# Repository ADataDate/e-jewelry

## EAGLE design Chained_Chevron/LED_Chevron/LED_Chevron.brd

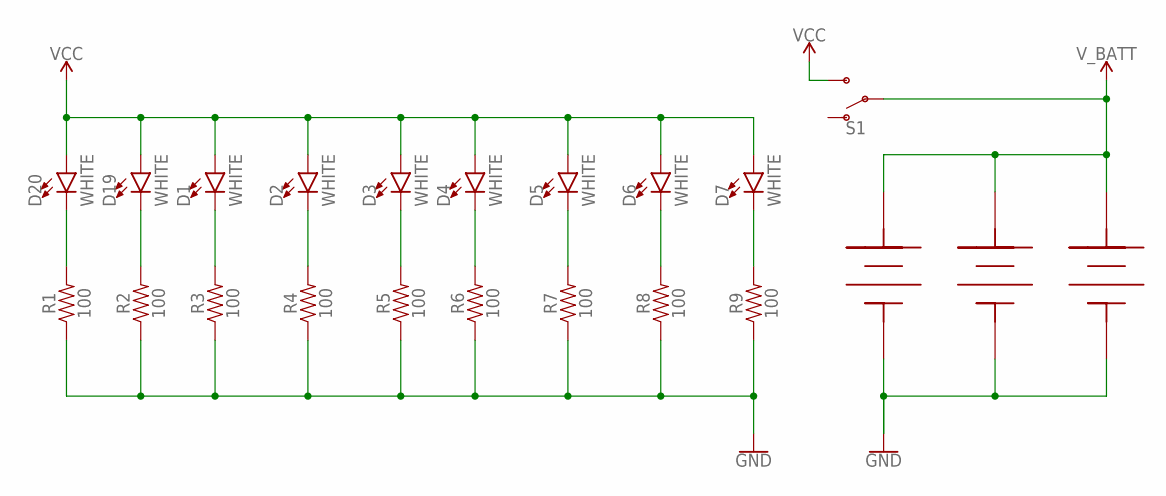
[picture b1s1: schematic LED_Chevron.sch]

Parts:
D1, D2, D3, D4, D5, D6, D7, D19, D20: WHITE; LED-1206
R1, R2, R3, R4, R5, R6, R7, R8, R9: 100; 0603
S1: SWITCH-SPDT-SMD-RIGHT-ANGLE; SWITCH_SPST_SMD_A
U$1, U$2, U$3: 7.8MM_COIN_CELL_BATTERY; 7.8MM_COIN_CELL_BATT

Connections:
GND: R1.1, R2.1, R3.1, R4.1, R5.1, R6.1, R7.1, R8.1, R9.1, U$1.GND (BATT-), U$2.GND (BATT-), U$3.GND (BATT-)
unnamed: D20.C, R1.2
unnamed: D19.C, R2.2
unnamed: D1.C, R3.2
unnamed: D2.C, R4.2
unnamed: D3.C, R5.2
unnamed: D4.C, R6.2
unnamed: D5.C, R7.2
unnamed: D6.C, R8.2
unnamed: D7.C, R9.2
VCC: D1.A, D2.A, D3.A, D4.A, D5.A, D6.A, D7.A, D19.A, D20.A, S1.3 (S)
V_BATT: S1.2, U$1.P$3 (BATT+), U$1.VBATT+ (BATT+), U$2.P$3 (BATT+), U$2.VBATT+ (BATT+), U$3.P$3 (BATT+), U$3.VBATT+ (BATT+)

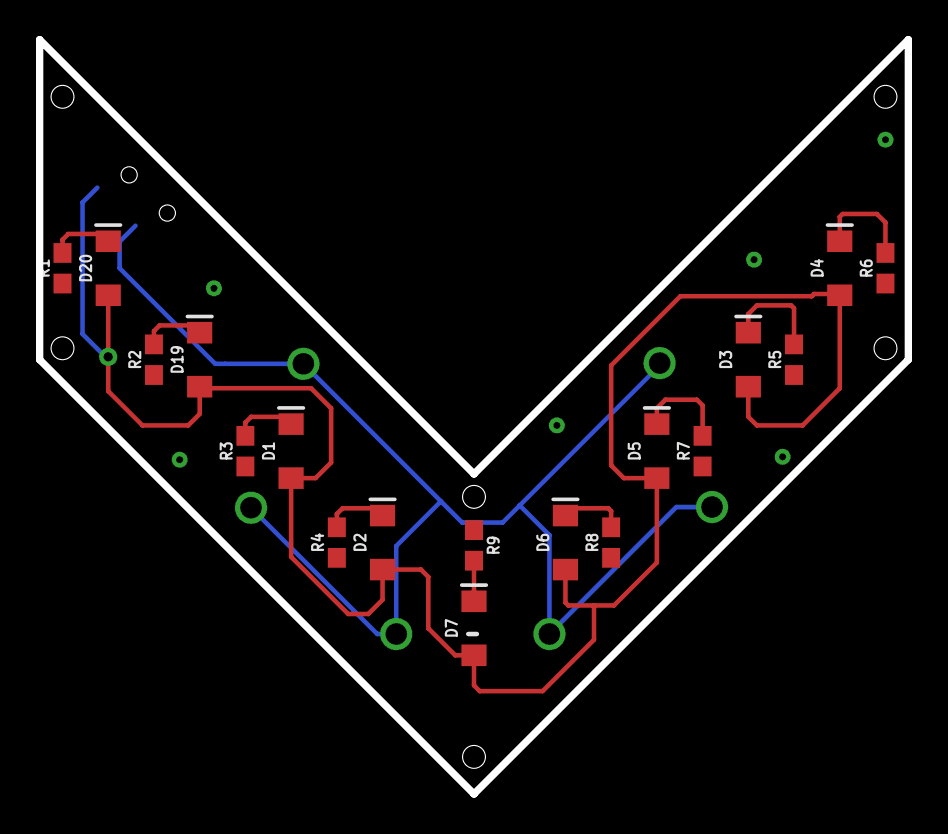
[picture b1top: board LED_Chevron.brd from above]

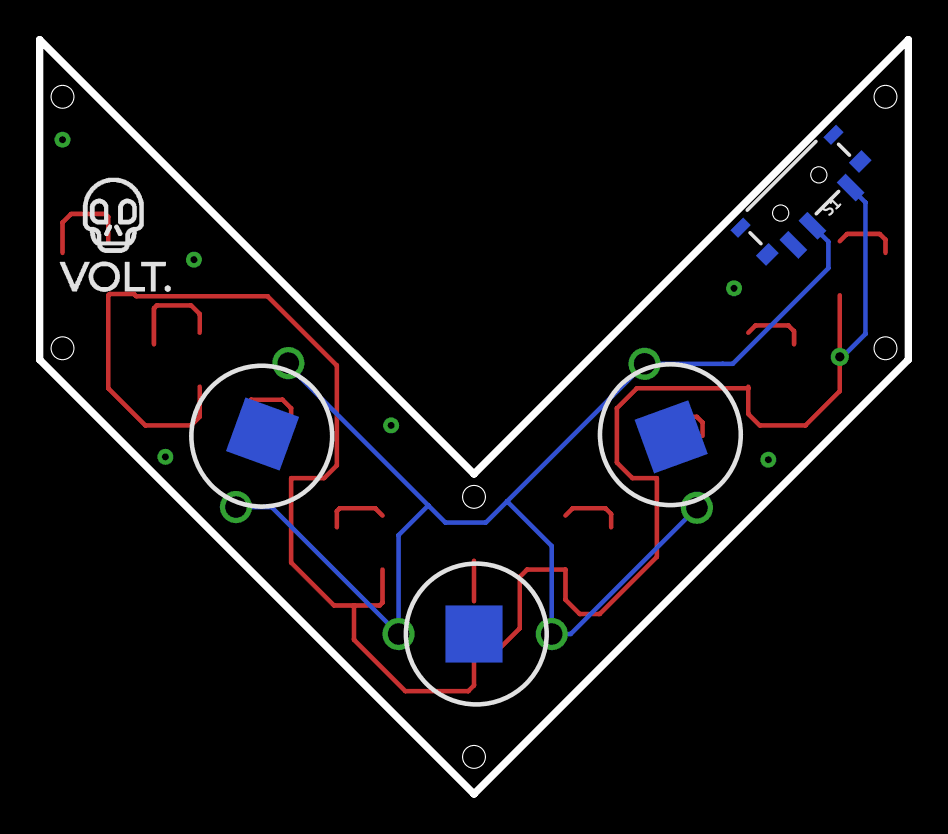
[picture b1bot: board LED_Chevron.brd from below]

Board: 2 copper layers, 48.3 x 41.9 mm, 23 parts (5 on the bottom side), 12 nets.

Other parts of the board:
U$5: VOLT##LOGO#WHITE_#1##PNG

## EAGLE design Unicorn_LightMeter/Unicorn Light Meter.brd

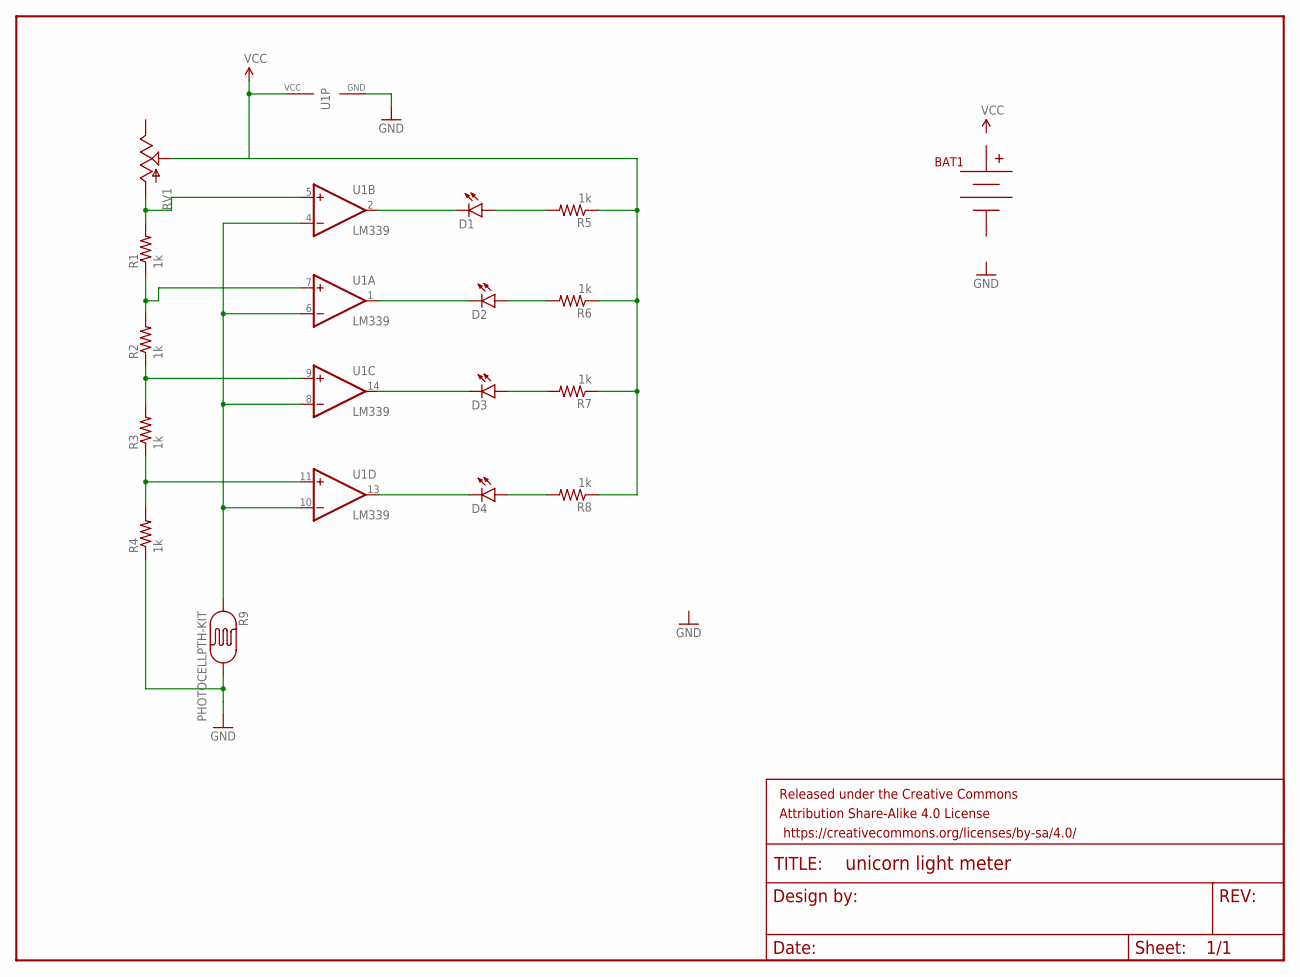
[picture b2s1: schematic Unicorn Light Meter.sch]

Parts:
BAT1: BC9VPCKIT_SOLDERMASK; BC9VPC_KIT
D1, D2, D3, D4: LED5MM
FRAME1: FRAME-LETTER; CREATIVE_COMMONS
R1, R2, R3, R4, R5, R6, R7, R8: 1k; AXIAL-0.3EZ
R9: PHOTOCELLPTH-KIT; PHOTOCELL-KIT
RV1: POT100K_3362U; 3362U
U1: LM339; TSSOP-14

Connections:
GND: R4.P$1 (1), R9.2, U1.12 (GND)
unnamed: D2.A, R6.P$2 (2)
unnamed: D3.A, R7.P$2 (2)
unnamed: D4.K (C), U1.13 (OUT)
unnamed: D3.K (C), U1.14 (OUT)
unnamed: D1.K (C), U1.2 (OUT)
unnamed: D2.K (C), U1.1 (OUT)
unnamed: D1.A, R5.P$2 (2)
unnamed: D4.A, R8.P$2 (2)
unnamed: R1.P$2 (2), RV1.P$3 (A), U1.5 (+IN)
unnamed: R1.P$1 (1), R2.P$2 (2), U1.7 (+IN)
unnamed: R2.P$1 (1), R3.P$2 (2), U1.9 (+IN)
unnamed: R3.P$1 (1), R4.P$2 (2), U1.11 (+IN)
unnamed: R9.1, U1.4 (-IN), U1.6 (-IN), U1.8 (-IN), U1.10 (-IN)
VCC: R5.P$1 (1), R6.P$1 (1), R7.P$1 (1), R8.P$1 (1), RV1.P$2 (S), U1.3 (VCC)

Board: 2 copper layers, 17 parts (1 on the bottom side), 15 nets, no tracks yet.

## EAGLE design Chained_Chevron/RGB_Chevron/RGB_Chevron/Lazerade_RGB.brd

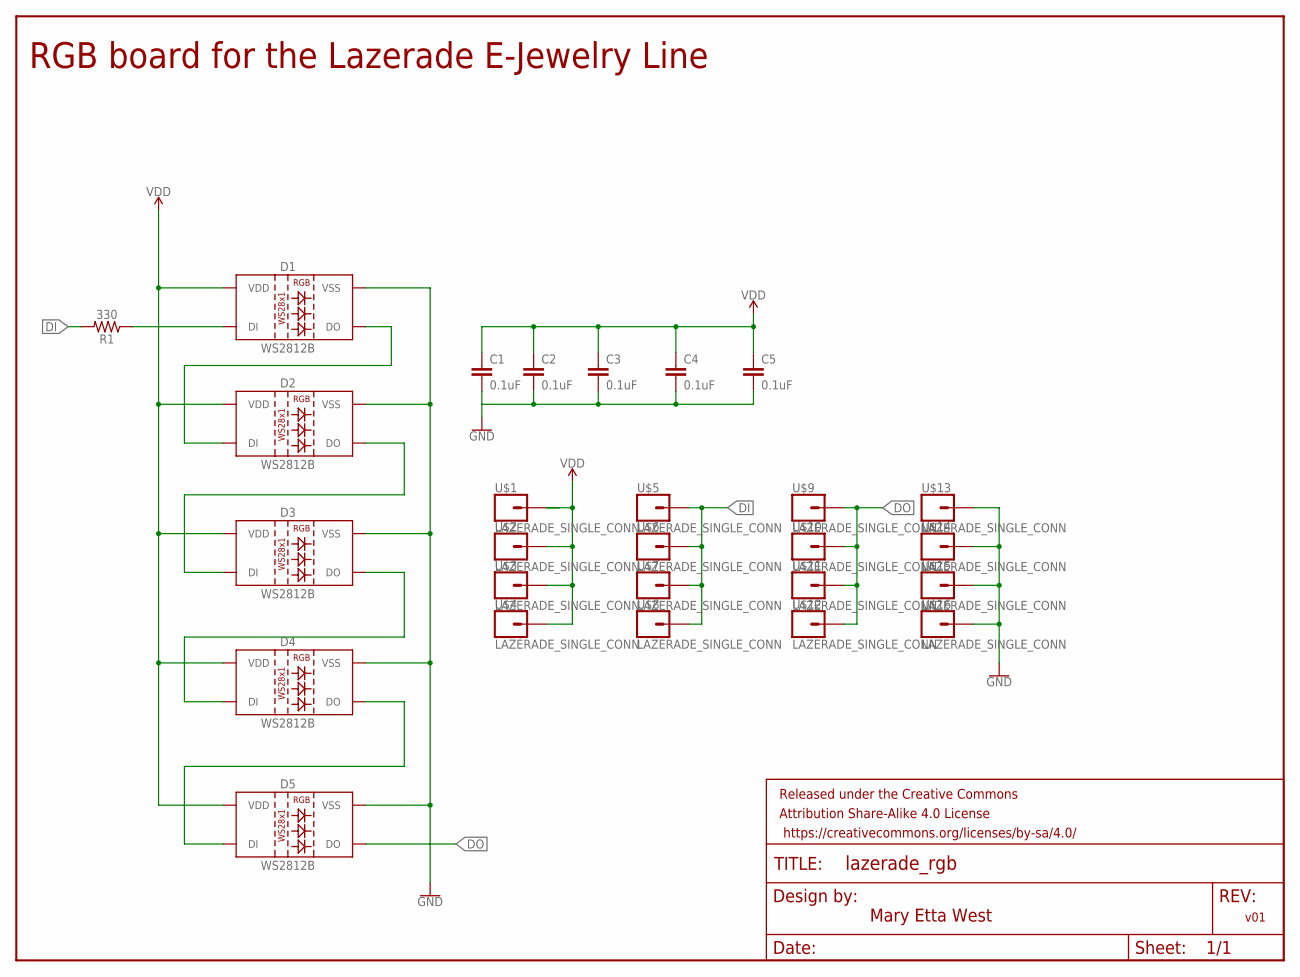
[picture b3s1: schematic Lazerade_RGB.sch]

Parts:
C1, C2, C3, C4, C5: 0.1uF; 0603
D1, D2, D3, D4, D5: WS2812B
FRAME1: FRAME-LETTER; CREATIVE_COMMONS
R1: 330; 0603
U$1, U$2, U$3, U$4, U$5, U$6, U$7, U$8, U$9, U$10, U$11, U$12, U$13, U$14, U$15, U$16: LAZERADE_SINGLE_CONN; SINLGE_PAD_CONNECT

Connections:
DI: R1.2, U$5.P$1, U$6.P$1, U$7.P$1, U$8.P$1
DI_U: D1.4 (DI), R1.1
DO: D5.2 (DO), U$9.P$1, U$10.P$1, U$11.P$1, U$12.P$1
GND: C1.2, C2.2, C3.2, C4.2, C5.2, D1.3 (VSS), D2.3 (VSS), D3.3 (VSS), D4.3 (VSS), D5.3 (VSS), U$13.P$1, U$14.P$1, U$15.P$1, U$16.P$1
unnamed: D1.2 (DO), D2.4 (DI)
unnamed: D2.2 (DO), D3.4 (DI)
unnamed: D3.2 (DO), D4.4 (DI)
unnamed: D4.2 (DO), D5.4 (DI)
VDD: C1.1, C2.1, C3.1, C4.1, C5.1, D1.1 (VDD), D2.1 (VDD), D3.1 (VDD), D4.1 (VDD), D5.1 (VDD), U$1.P$1, U$2.P$1, U$3.P$1, U$4.P$1

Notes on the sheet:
Mary Etta West
v01
RGB board for the Lazerade E-Jewelry Line

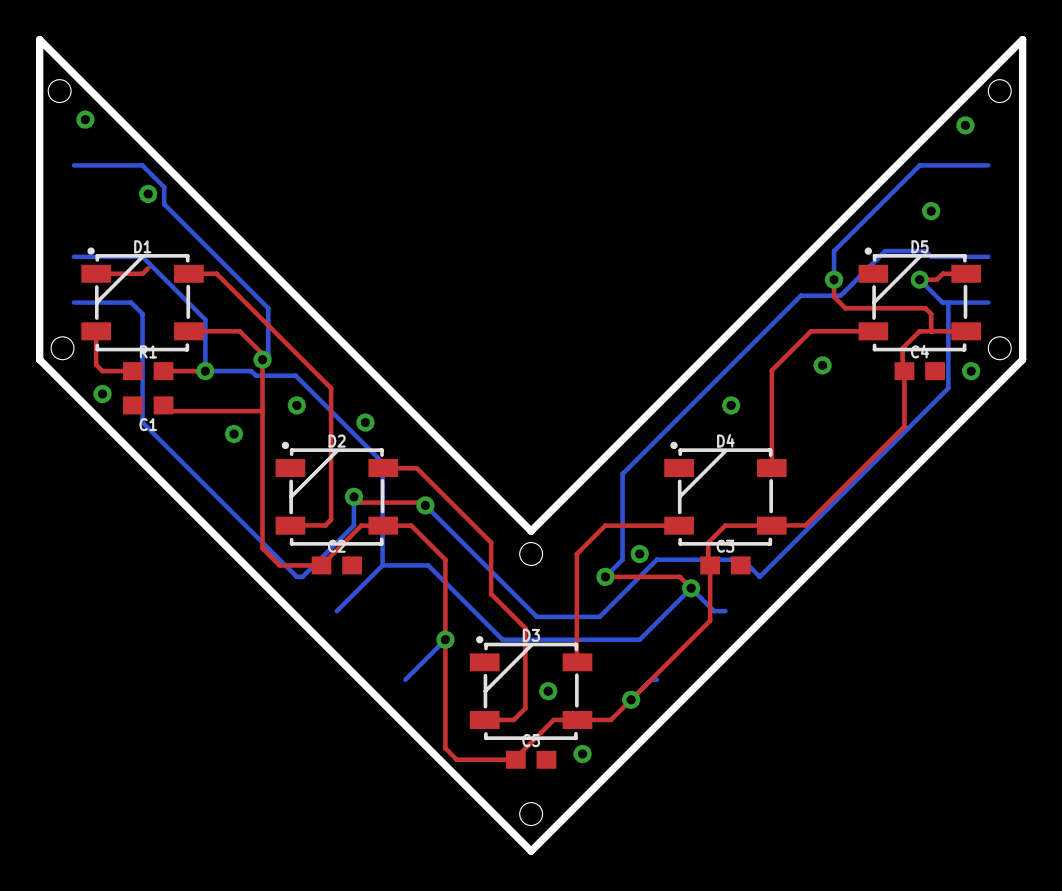
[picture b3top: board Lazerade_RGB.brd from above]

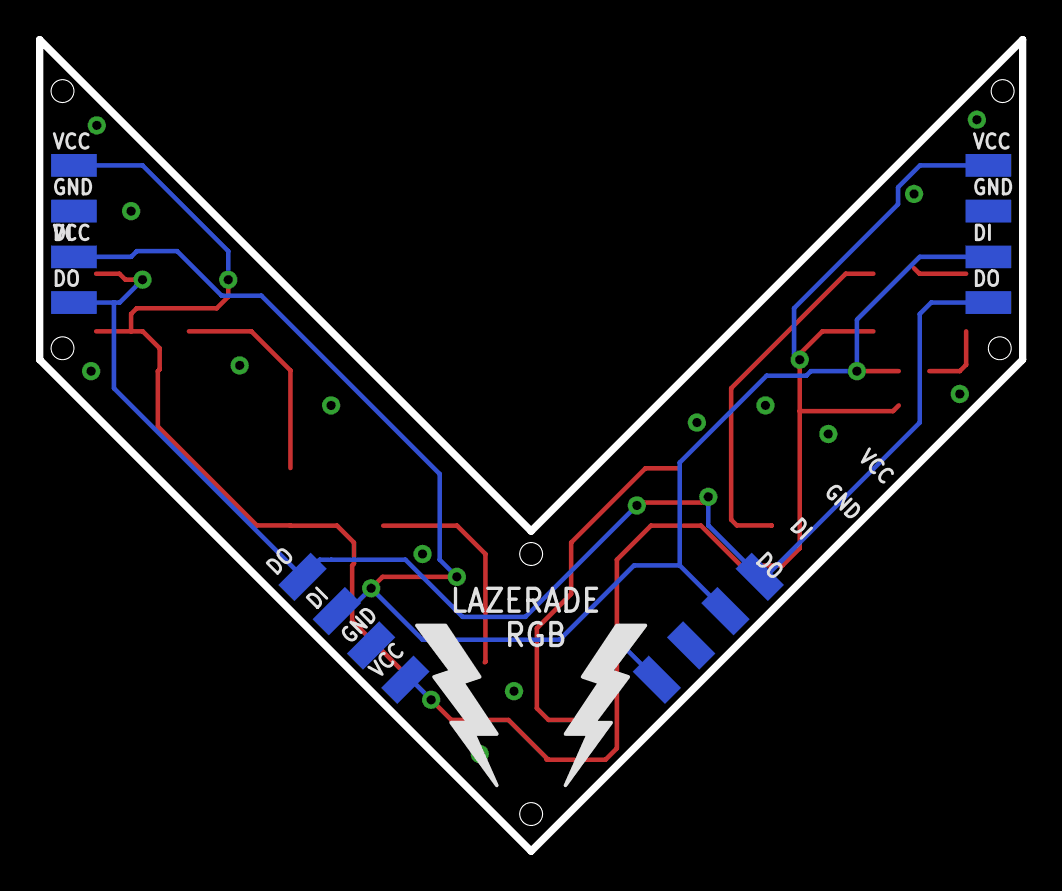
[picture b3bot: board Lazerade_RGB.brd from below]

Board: 2 copper layers, 54.6 x 45.1 mm, 28 parts (16 on the bottom side), 9 nets.

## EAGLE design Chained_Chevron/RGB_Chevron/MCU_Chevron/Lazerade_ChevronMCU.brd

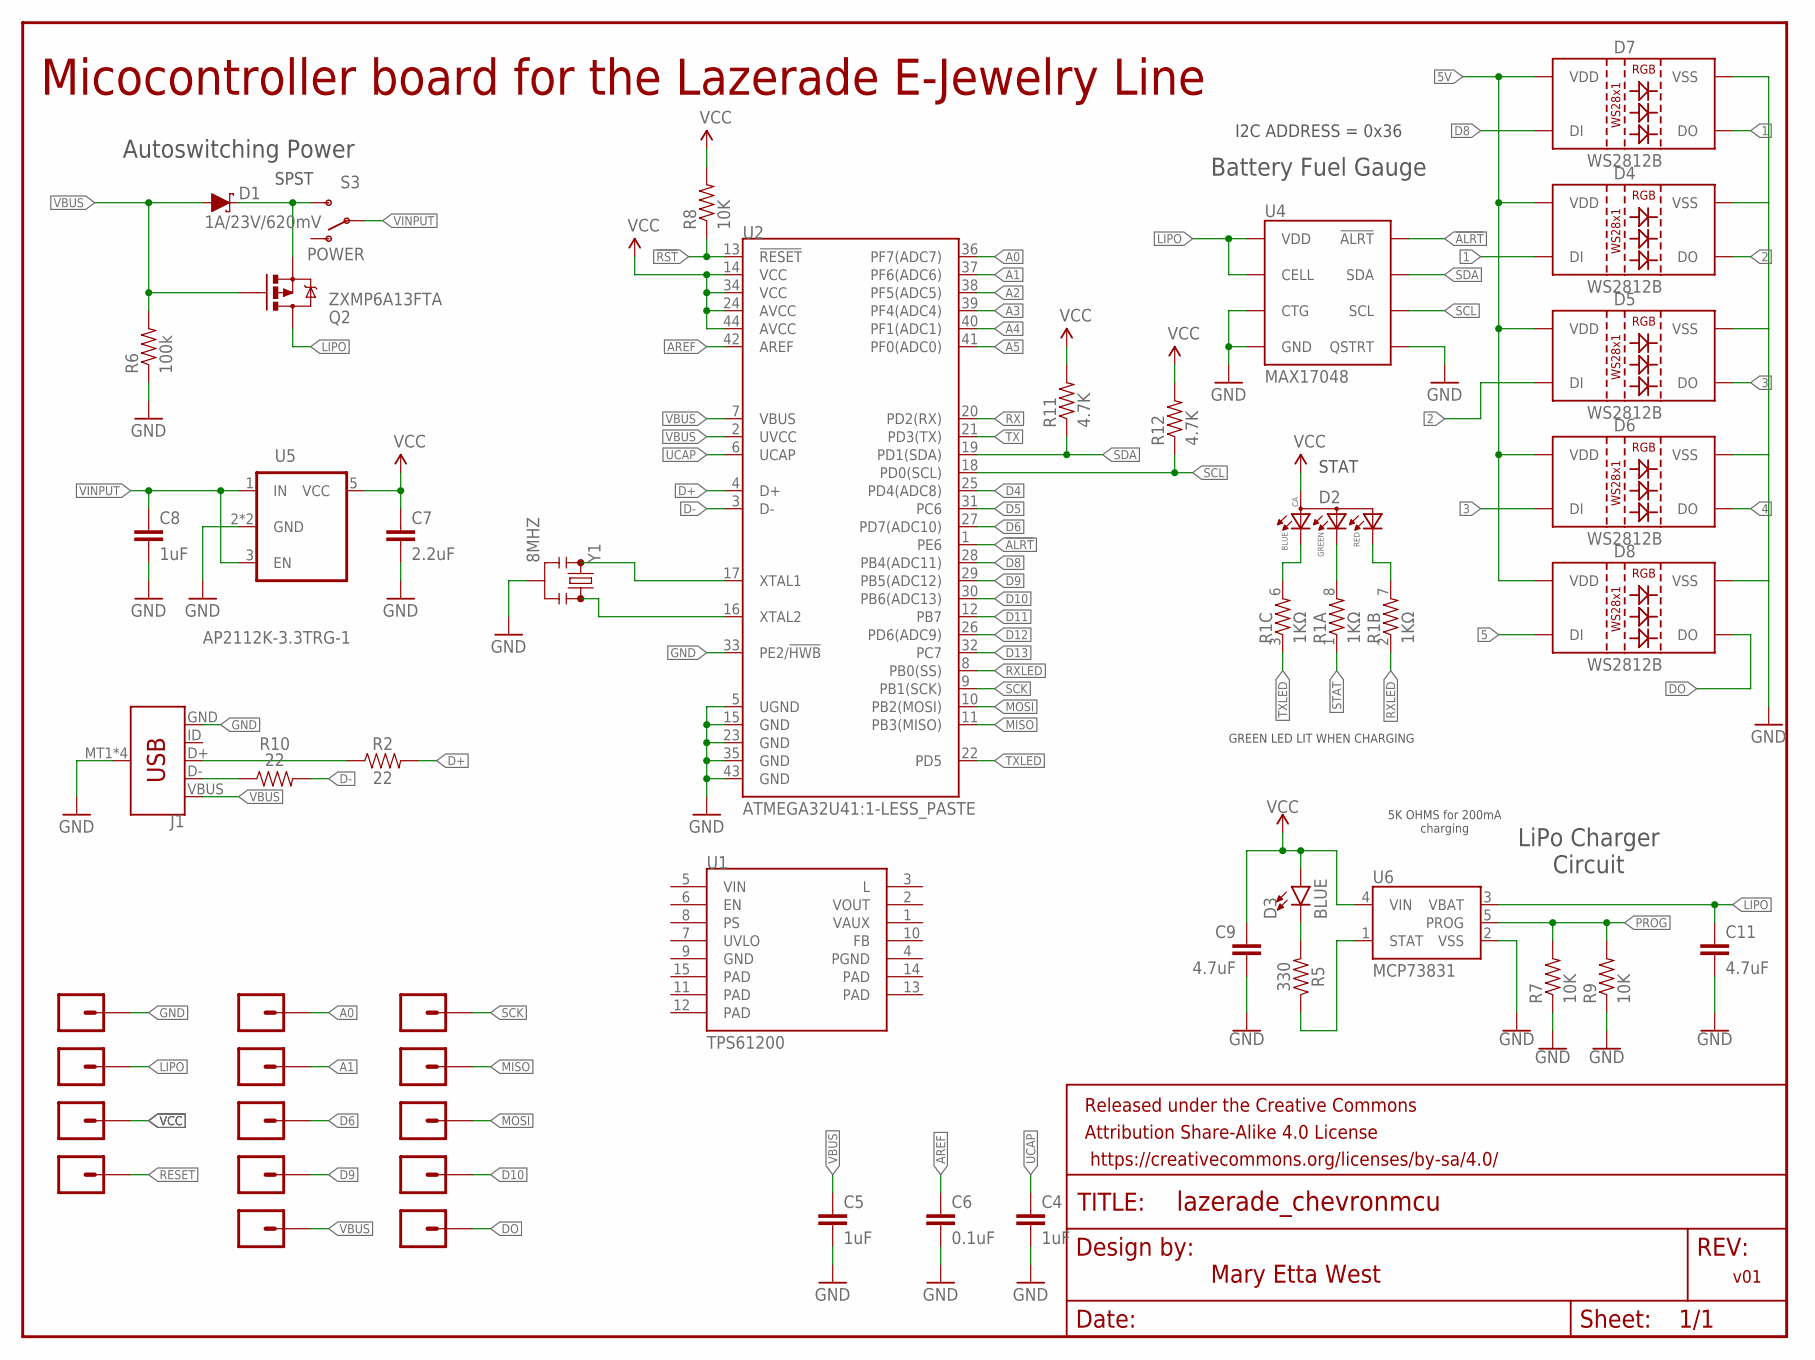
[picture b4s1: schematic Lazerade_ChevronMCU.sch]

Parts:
C4, C5, C8: 1uF; 0603-CAP
C6: 0.1uF; 0603-CAP
C7: 2.2uF; 0603-CAP
C9, C11: 4.7uF; 0603
D1: 1A/23V/620mV; SOD-323
D2: 0.13_RGB_LEDPLCC; P-LCC-4-3
D3: BLUE; LED-0603
D4, D5, D6, D7, D8: WS2812B
FRAME1: FRAME-LETTER; CREATIVE_COMMONS
J1: USB_MICRO-B_SMT; USB-MICROB
Q2: ZXMP6A13FTA; SOT23-3@1
R1: 1KΩ; 0603-ARV
R2, R10: 22; 0603
R5: 330; 0603
R6: 100k; 0603-RES
R7, R8, R9: 10K; 0603-RES
R11, R12: 4.7K; 0603-RES
S3: POWER; SWITCH-SPST-SMD-A
U1: TPS61200; QFN-10_PAD
U2: ATMEGA32U41:1-LESS_PASTE; QFN-44-NOPAD_1:1-LESS_PASTE
U4: MAX17048; DFN-8
U5: AP2112K-3.3TRG-1; SOT23-5
U6: MCP73831; SOT23-5
U$1, U$2, U$3, U$4, U$5, U$7, U$8, U$9, U$10, U$11, U$12, U$13, U$14, U$18: LAZERADE_SINGLE_CONN; SINLGE_PAD_CONNECT
Y1: 8MHZ; RESONATOR-SMD

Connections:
1: D4.4 (DI), D7.2 (DO)
2: D4.2 (DO), D5.4 (DI)
3: D5.2 (DO), D6.4 (DI)
4: D6.2 (DO)
5: D8.4 (DI)
5V: D4.1 (VDD), D5.1 (VDD), D6.1 (VDD), D7.1 (VDD), D8.1 (VDD)
!ALRT: U2.1 (PE6), U4.P$5 (!ALRT)
!RST: R8.1, U2.13 (!RESET)
A0: U2.36 (PF7(ADC7)), U$1.P$1
A1: U2.37 (PF6(ADC6)), U$2.P$1
A2: U2.38 (PF5(ADC5))
A3: U2.39 (PF4(ADC4))
A4: U2.40 (PF1(ADC1))
A5: U2.41 (PF0(ADC0))
AREF: C6.1, U2.42 (AREF)
D4: U2.25 (PD4(ADC8))
D5: U2.31 (PC6)
D6: U2.27 (PD7(ADC10)), U$3.P$1
D8: D7.4 (DI), U2.28 (PB4(ADC11))
D9: U2.29 (PB5(ADC12)), U$4.P$1
D10: U2.30 (PB6(ADC13)), U$11.P$1
D11: U2.12 (PB7)
D12: U2.26 (PD6(ADC9))
D13: U2.32 (PC7)
D+: R2.2, U2.4 (D+)
D-: R10.2, U2.3 (D-)
DO: D8.2 (DO), U$18.P$1
GND: C4.2, C5.2, C6.2, C7.2, C8.2, C9.2, C11.2, D4.3 (VSS), D5.3 (VSS), D6.3 (VSS), D7.3 (VSS), D8.3 (VSS), J1.GND, J1.MT1 (SHIELD), J1.MT2 (SHIELD), J1.P$1 (SHIELD), J1.P$2 (SHIELD), R6.1, R7.1, R9.1, U2.5 (UGND), U2.15 (GND), U2.23 (GND), U2.33 (PE2/!HWB), U2.35 (GND), U2.43 (GND), U4.P$1 (CTG), U4.P$4 (GND), U4.P$6 (QSTRT), U4.P$9 (GND), U5.2 (GND), U5.4 (GND), U6.2 (VSS), U$13.P$1, Y1.2
INMOSFET: D1.C, Q2.2 (S), S3.3 (S)
LIPO: C11.1, Q2.3 (D), U4.P$2 (CELL), U4.P$3 (VDD), U6.3 (VBAT), U$14.P$1
MISO: U2.11 (PB3(MISO)), U$9.P$1
MOSI: U2.10 (PB2(MOSI)), U$10.P$1
unnamed: J1.D-, R10.1
unnamed: D2.3 (BLUE), R1.6 (2)
unnamed: D2.2 (GREEN), R1.8 (2)
unnamed: R5.1, U6.1 (STAT)
unnamed: D3.C, R5.2
unnamed: J1.D+, R2.1
unnamed: D2.1 (RED), R1.7 (2)
PROG: R7.2, R9.2, U6.5 (PROG)
RESET: U$12.P$1
RX: U2.20 (PD2(RX))
RXLED: R1.2 (1), U2.8 (PB0(SS))
SCK: U2.9 (PB1(SCK)), U$8.P$1
SCL: R12.1, U2.18 (PD0(SCL)), U4.P$7 (SCL)
SDA: R11.1, U2.19 (PD1(SDA)), U4.P$8 (SDA)
STAT: R1.1
TX: U2.21 (PD3(TX))
TXLED: R1.3 (1), U2.22 (PD5)
UCAP: C4.1, U2.6 (UCAP)
VBUS: C5.1, D1.A, J1.VBUS, Q2.1 (G), R6.2, U2.2 (UVCC), U2.7 (VBUS), U$5.P$1
VCC: C7.1, C9.1, D2.4 (ANODE), D3.A, R8.2, R11.2, R12.2, U2.14 (VCC), U2.24 (AVCC), U2.34 (VCC), U2.44 (AVCC), U5.5 (VCC), U6.4 (VIN), U$7.P$1
VINPUT: C8.1, S3.2, U5.1 (IN), U5.3 (EN)
X1: U2.17 (XTAL1), Y1.3
X2: U2.16 (XTAL2), Y1.1

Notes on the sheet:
Mary Etta West
v01
Micocontroller board for the Lazerade E-Jewelry Line
SPST
LiPo Charger Circuit
Battery Fuel Gauge
Autoswitching Power
I2C ADDRESS = 0x36
STAT
GREEN LED LIT WHEN CHARGING
5K OHMS for 200mA charging

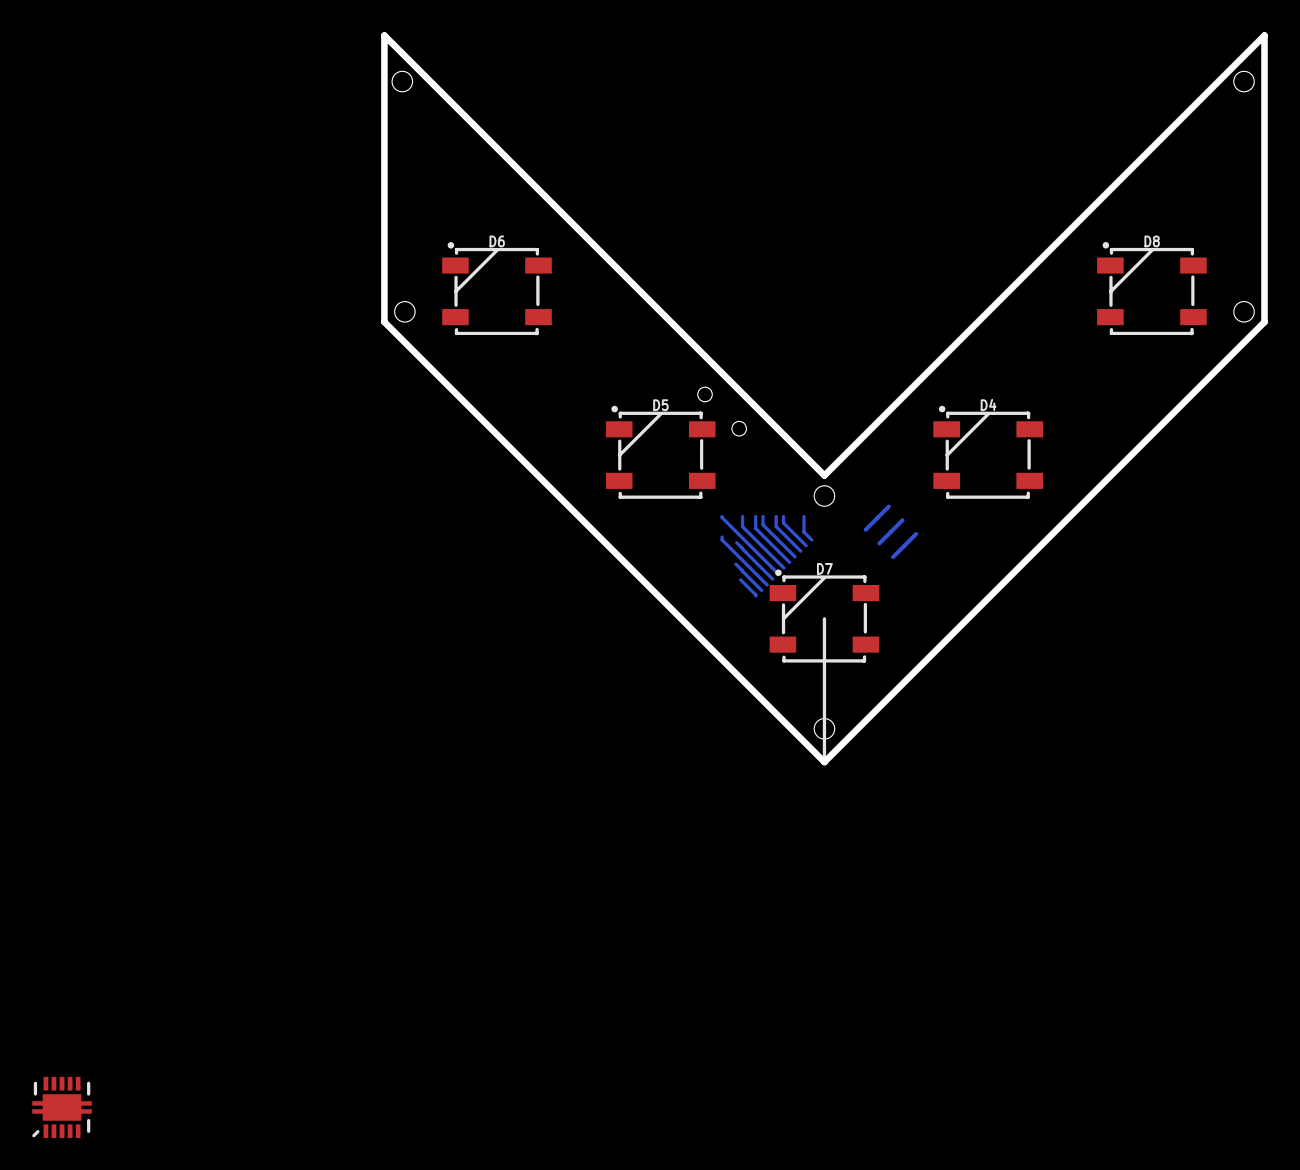
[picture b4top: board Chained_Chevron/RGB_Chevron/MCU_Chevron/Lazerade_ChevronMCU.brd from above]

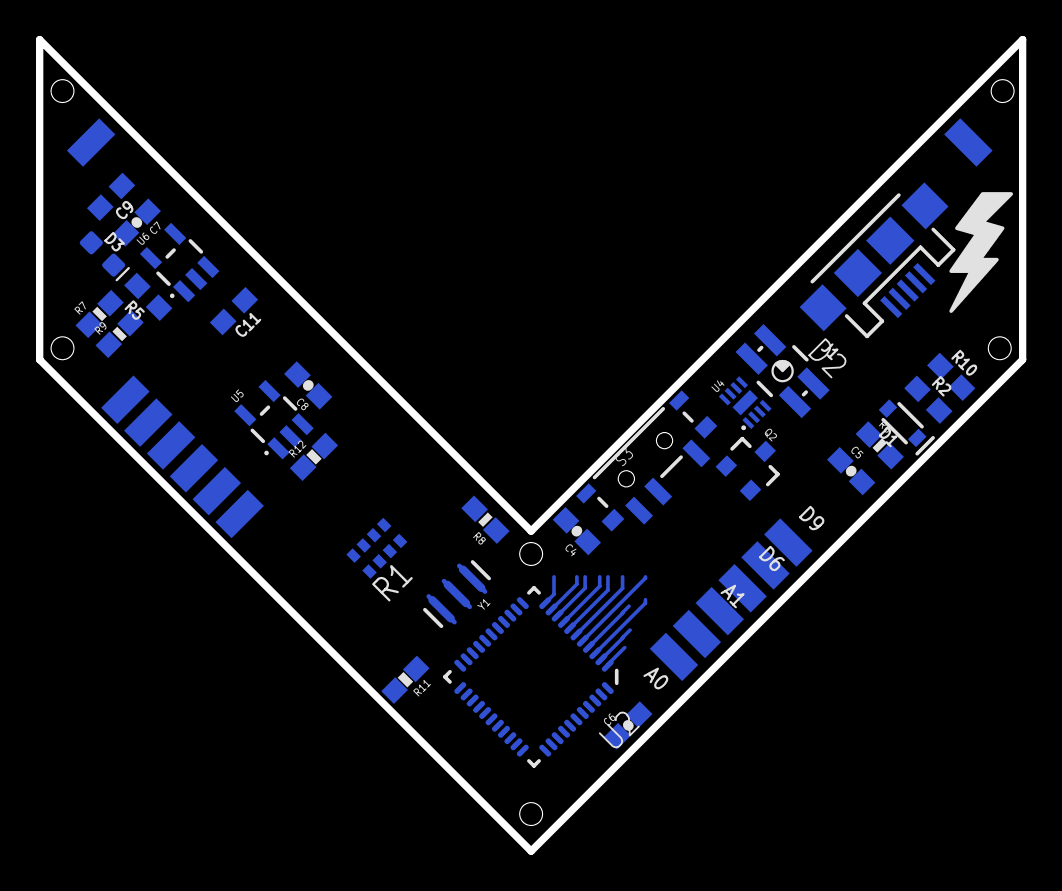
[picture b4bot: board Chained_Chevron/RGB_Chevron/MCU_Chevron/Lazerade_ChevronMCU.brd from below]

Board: 2 copper layers, 54.6 x 45.1 mm, 49 parts (42 on the bottom side), 40 nets.

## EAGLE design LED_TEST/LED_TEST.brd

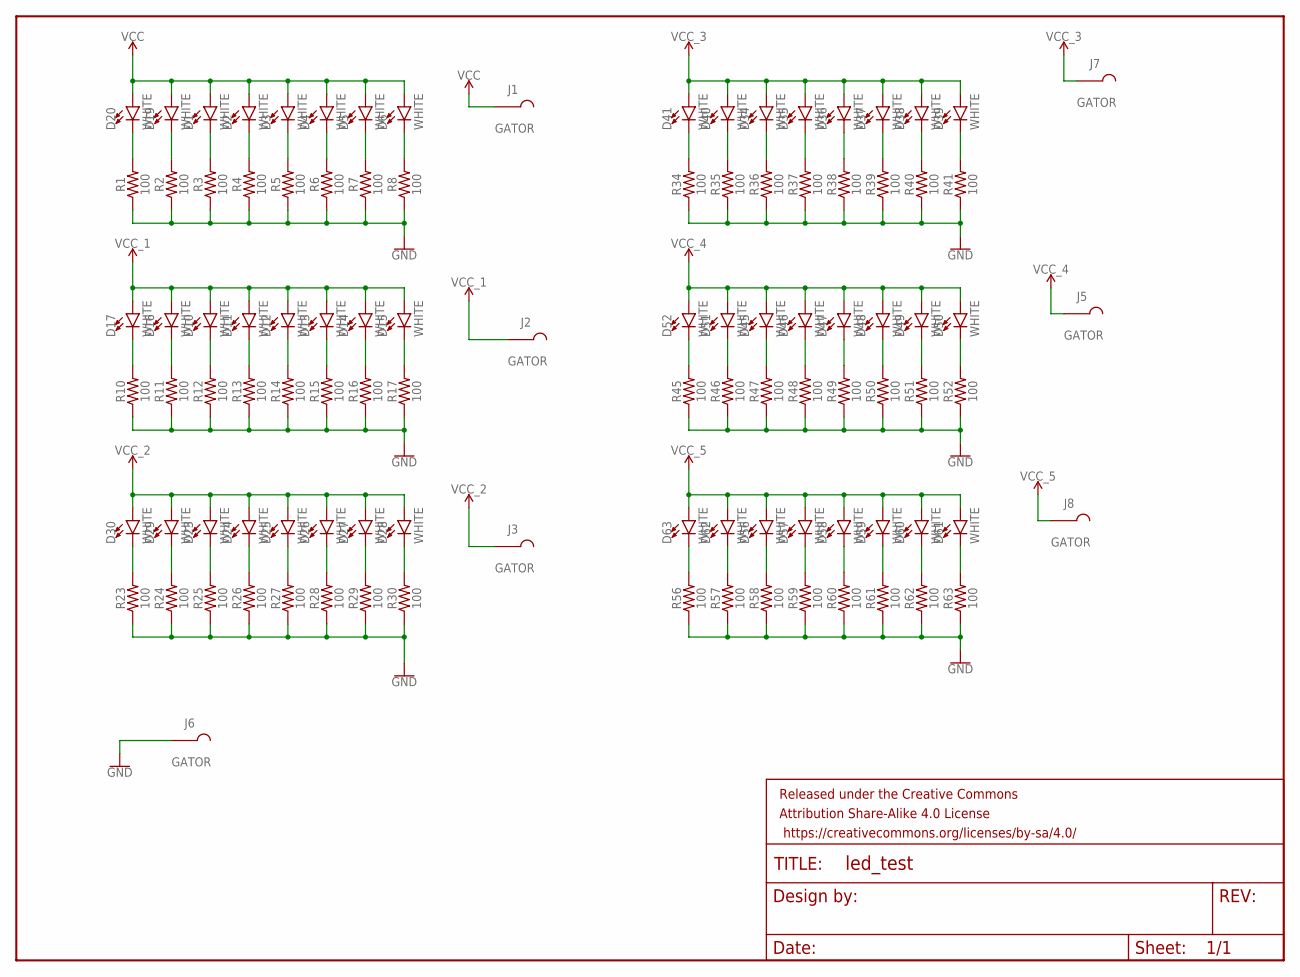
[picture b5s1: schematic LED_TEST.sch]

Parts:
D1, D2, D3, D4, D5, D6, D10, D11, D12, D13, D14, D15, D16, D17, D19, D20, D23, D24, D25, D26, D27, D28, D29, D30, D34, D35, D36, D37, D38, D39, D40, D41, D45, D46, D47, D48, D49, D50, D51, D52, D56, D57, D58, D59, D60, D61, D62, D63: WHITE; LED-1206
FRAME1: FRAME-LETTER; CREATIVE_COMMONS
J1, J2, J3, J5, J6, J7, J8: GATOR
R1, R2, R3, R4, R5, R6, R7, R8, R10, R11, R12, R13, R14, R15, R16, R17, R23, R24, R25, R26, R27, R28, R29, R30, R34, R35, R36, R37, R38, R39, R40, R41, R45, R46, R47, R48, R49, R50, R51, R52, R56, R57, R58, R59, R60, R61, R62, R63: 100; 0603

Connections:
GND: J6.P$1, J6.P$2, R1.1, R2.1, R3.1, R4.1, R5.1, R6.1, R7.1, R8.1, R10.1, R11.1, R12.1, R13.1, R14.1, R15.1, R16.1, R17.1, R23.1, R24.1, R25.1, R26.1, R27.1, R28.1, R29.1, R30.1, R34.1, R35.1, R36.1, R37.1, R38.1, R39.1, R40.1, R41.1, R45.1, R46.1, R47.1, R48.1, R49.1, R50.1, R51.1, R52.1, R56.1, R57.1, R58.1, R59.1, R60.1, R61.1, R62.1, R63.1
unnamed: D20.C, R1.2
unnamed: D19.C, R2.2
unnamed: D1.C, R3.2
unnamed: D2.C, R4.2
unnamed: D3.C, R5.2
unnamed: D4.C, R6.2
unnamed: D5.C, R7.2
unnamed: D6.C, R8.2
unnamed: D17.C, R10.2
unnamed: D16.C, R11.2
unnamed: D10.C, R12.2
unnamed: D11.C, R13.2
unnamed: D12.C, R14.2
unnamed: D13.C, R15.2
unnamed: D14.C, R16.2
unnamed: D15.C, R17.2
unnamed: D30.C, R23.2
unnamed: D29.C, R24.2
unnamed: D23.C, R25.2
unnamed: D24.C, R26.2
unnamed: D25.C, R27.2
unnamed: D26.C, R28.2
unnamed: D27.C, R29.2
unnamed: D28.C, R30.2
unnamed: D41.C, R34.2
unnamed: D40.C, R35.2
unnamed: D34.C, R36.2
unnamed: D35.C, R37.2
unnamed: D36.C, R38.2
unnamed: D37.C, R39.2
unnamed: D38.C, R40.2
unnamed: D39.C, R41.2
unnamed: D52.C, R45.2
unnamed: D51.C, R46.2
unnamed: D45.C, R47.2
unnamed: D46.C, R48.2
unnamed: D47.C, R49.2
unnamed: D48.C, R50.2
unnamed: D49.C, R51.2
unnamed: D50.C, R52.2
unnamed: D63.C, R56.2
unnamed: D62.C, R57.2
unnamed: D56.C, R58.2
unnamed: D57.C, R59.2
unnamed: D58.C, R60.2
unnamed: D59.C, R61.2
unnamed: D60.C, R62.2
unnamed: D61.C, R63.2
VCC: D1.A, D2.A, D3.A, D4.A, D5.A, D6.A, D19.A, D20.A, J1.P$1, J1.P$2
VCC_1: D10.A, D11.A, D12.A, D13.A, D14.A, D15.A, D16.A, D17.A, J2.P$1, J2.P$2
VCC_2: D23.A, D24.A, D25.A, D26.A, D27.A, D28.A, D29.A, D30.A, J3.P$1, J3.P$2
VCC_3: D34.A, D35.A, D36.A, D37.A, D38.A, D39.A, D40.A, D41.A, J7.P$1, J7.P$2
VCC_4: D45.A, D46.A, D47.A, D48.A, D49.A, D50.A, D51.A, D52.A, J5.P$1, J5.P$2
VCC_5: D56.A, D57.A, D58.A, D59.A, D60.A, D61.A, D62.A, D63.A, J8.P$1, J8.P$2

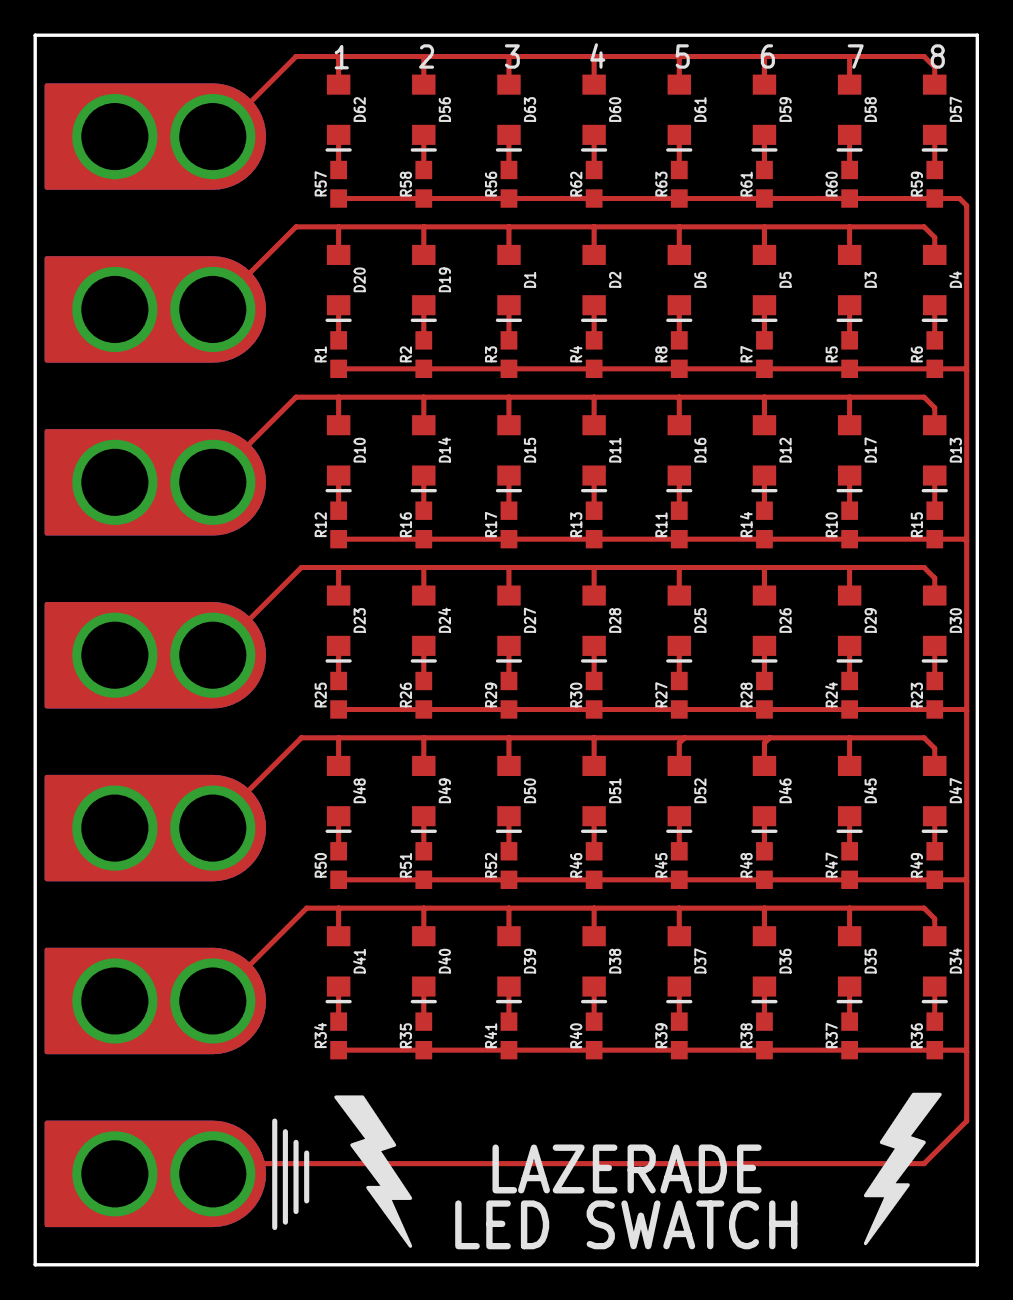
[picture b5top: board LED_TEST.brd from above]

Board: 2 copper layers, 56.2 x 73.3 mm, 104 parts (0 on the bottom side), 55 nets.

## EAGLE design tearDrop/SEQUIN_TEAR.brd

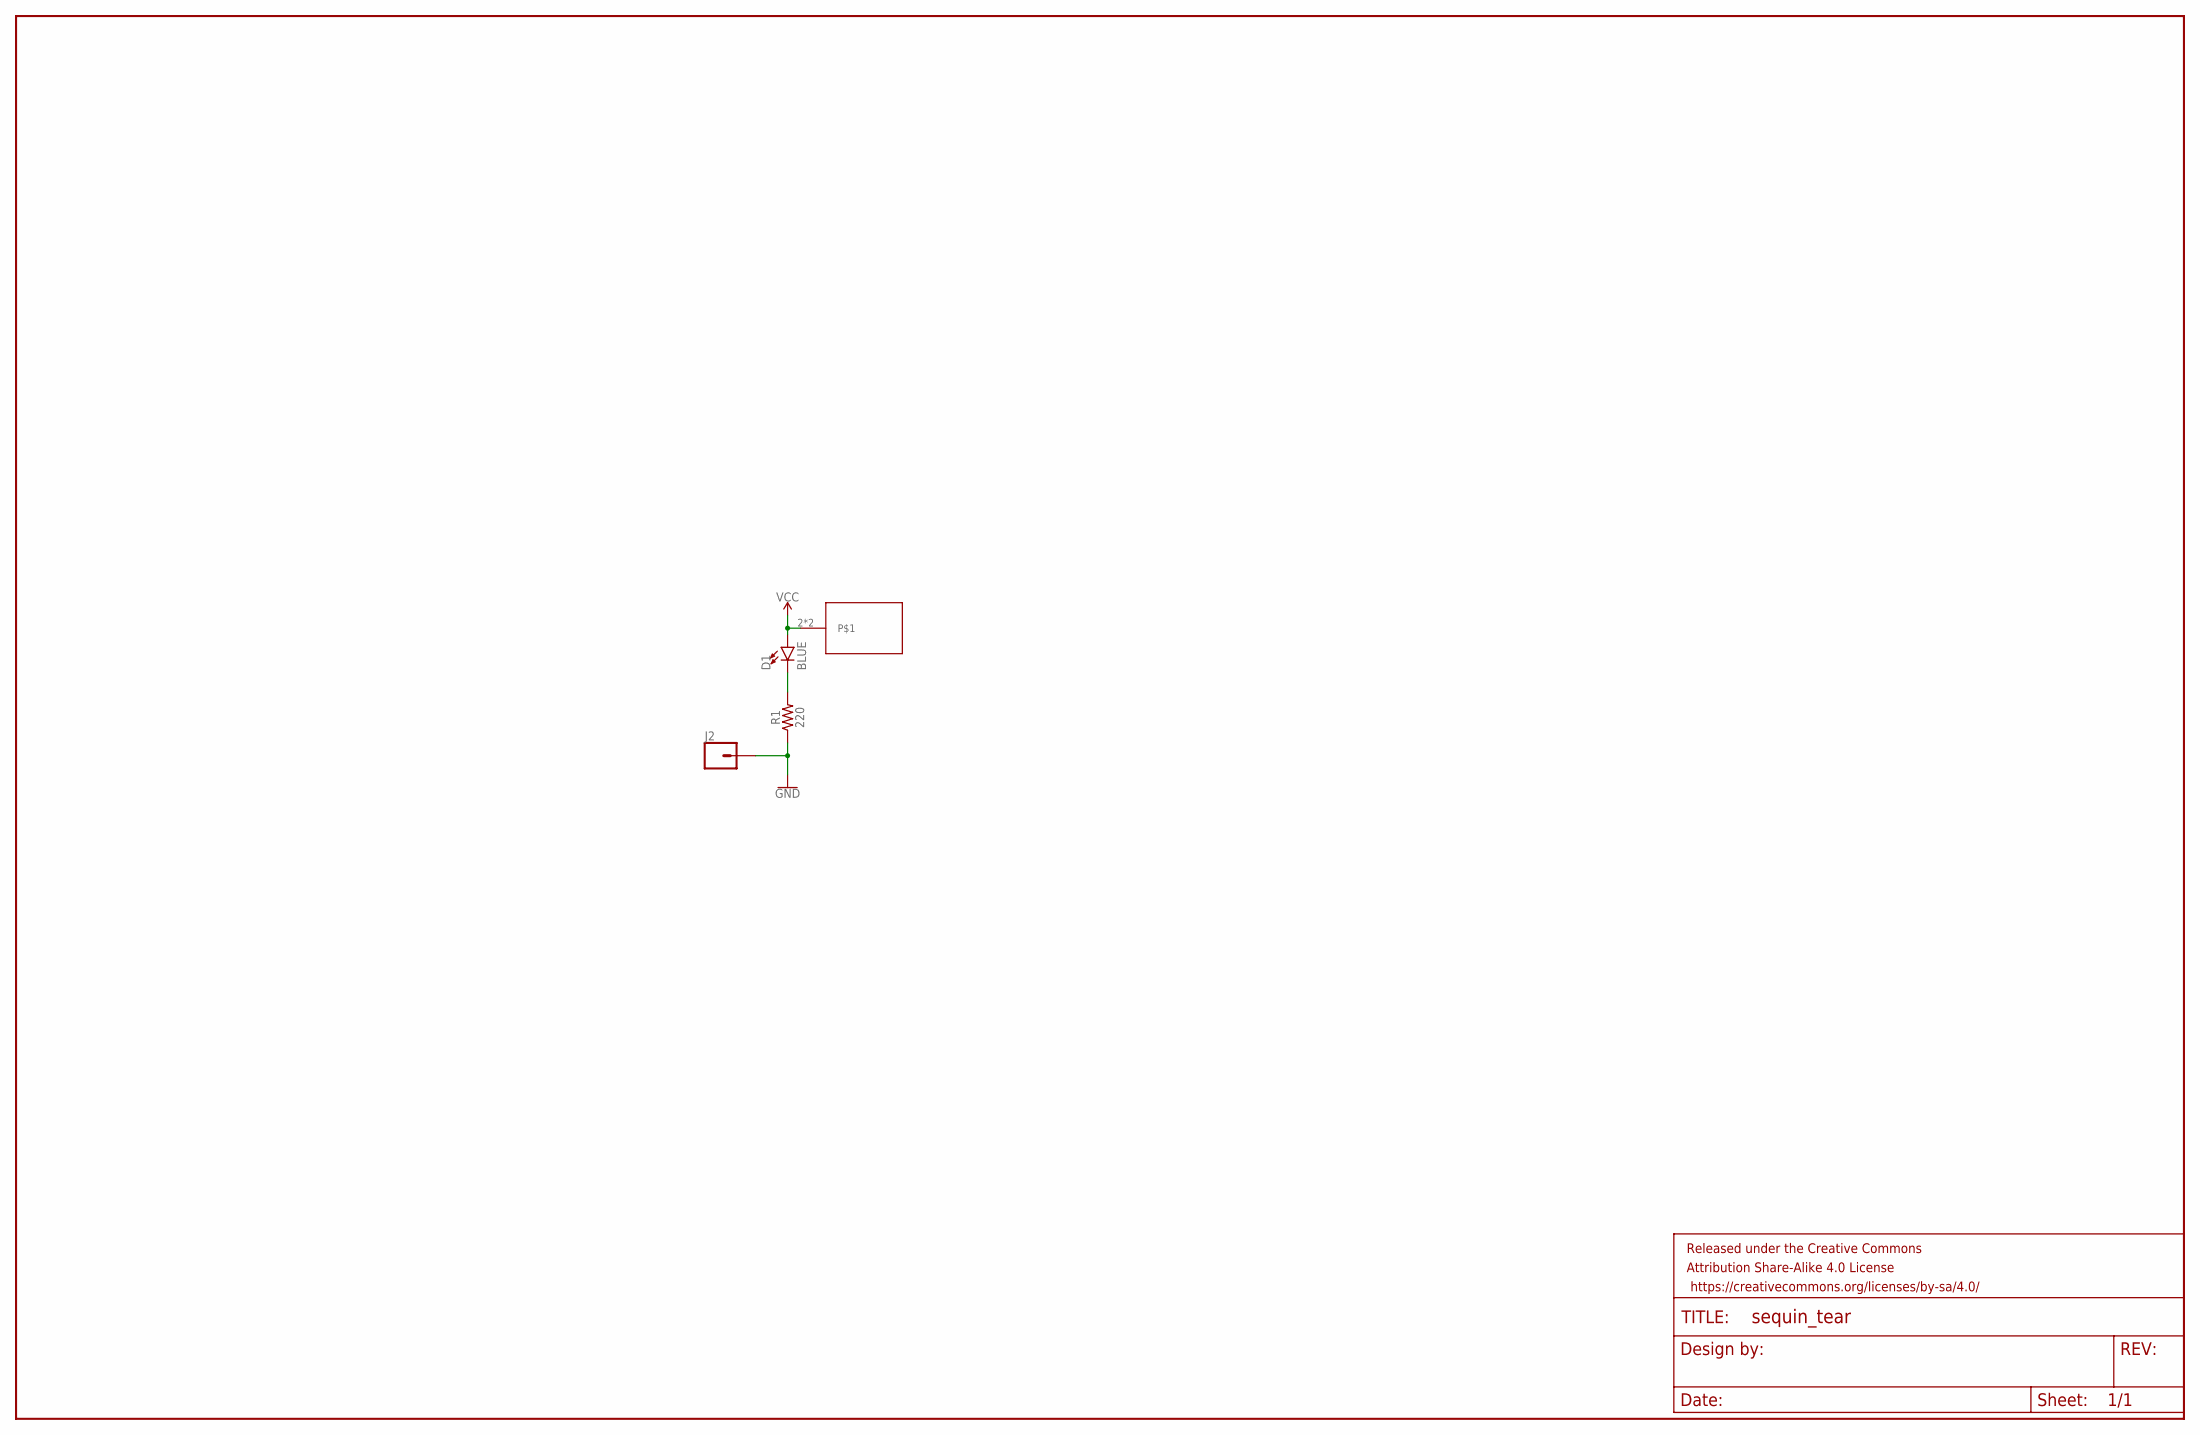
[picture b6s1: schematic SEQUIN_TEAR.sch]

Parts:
D1: BLUE; LED-1206
FRAME1: FRAME-LEDGER; CREATIVE_COMMONS
J2: CONN_01SPRING-CONN; SPRING-CONNECTOR
R1: 220; 0603
U$1: TEARDROP

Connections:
GND: J2.P$2, R1.1
unnamed: D1.C, R1.2
VCC: D1.A, U$1.2, U$1.VCC

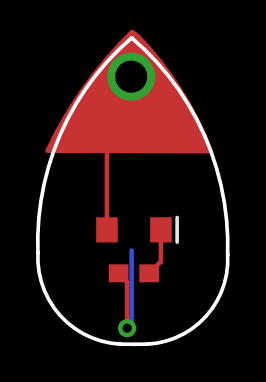
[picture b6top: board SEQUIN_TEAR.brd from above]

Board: 2 copper layers, 10.5 x 17.0 mm, 5 parts (1 on the bottom side), 3 nets.

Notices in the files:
parts and their libraries:
SparkFun-LED: Licensing: Creative Commons ShareAlike 4.0 International - https://creativecommons.org/licenses/by-sa/4.0
SparkFun-Aesthetics: Released under the Creative Commons Attribution Share-Alike 4.0 License
SparkFun-Aesthetics: https://creativecommons.org/licenses/by-sa/4.0
